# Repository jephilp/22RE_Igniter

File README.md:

# Igniter Module for Toyota VAST Engines

Hi there! This is a repository first for the 22RE igniter module, and eventually most Toyota VAST igniters. It is currently a work in progress.

# What is VAST?

VAST stands for variable advance spark timing system. It's the system Toyota uses on a ton of their older vehicles. 

## How does it work?

Here's a **very generalized** diagram to get a better idea of how the system works:

```mermaid
graph LR
A[ECU] -- IGf --> B[Igniter Module]
B -- IGt --> A
B -- NE --> A
B --> C((Ignition Coil))
C --> D{Engine}
D -- VR Signals --> B
```
## Know the flow

The way that everything ties together is fairly simple:

- At startup, the igniter assumes a locked timing. This is stated in the manual for each engine.
- The VR signal is sent to the igniter.
  - The signal is converted from a sine to a square wave by the igniter (NE).
  - NE is used to reference the spark timing for the igniter.
  - NE is also sent to the ECU for spark timing reference.
 - The ECU begins sending the IGt (Ignition Time) signal to the igniter
   - The igniter uses the **FALLING EDGE** of this signal to trigger the coil.
   - The igniter **STILL CONTROLS DWELL**. 
   - The style of signal depends on year, make and model.
 - The ECU expects to receive the IGf (Ignition Fired) signal from the igniter.
   - If the ECU does not receive this signal it will assume locked timing and issue a CEL.
   - The style of signal depends on year, make and model. 
   - This is the critical signal that blocks most ignition coil swaps.
   - The igniter can disable this signal to signify ignition issues like a bad coil. 
 - The ECU receives the signal
   - Once the signal is received within a certain time, the ECU will assume all is good.
   - The engine will run with no trouble codes as long as the timing is correct.

## Spoofing our signal

If you roam around forums long enough, you'll find that many people have figured out a way to spoof this signal. This just involves tying the IGt signal to a diode and transistor. This generates our "spoofed" IGf signal.

While this can and does work, it's not the best option. We are losing a lot of capability, and you will still need some type of module to control the coils. 

There is a better way!

## Recreating our signal

There are two main ways that our IGf signal is generated:

1. Use the overvoltage on the primary side of the coil to trigger a multivibrator that creates our signal **after** IGt.
2. Use the current through the coil to create a ramped signal **during** IGt. 

Then in the middle of all of this is our checking scheme. Failing coils won't have enough overvoltage or won't flow enough current quick enough. So ideally when our coils are failing we stop sending the IGf signal to tell the ECU to trip a CEL. 

We can create our signal using analog "dumb" logic or we can use a microcontroller for "smart" logic. Smart logic will be easier for creating a more universal module that will work with more models and allow for some tweaking.
 
## Other Options

There are some other options if your igniter fails:

- Spend $300+ on a used module from eBay or a forum member.
- Spend $500+ on an NOS module if you can find it, or import one.
- Delete the igniter system with something similar. This is only possible on some systems (22R).
- Replace the entire ECU with another that does not need IGf.
- Find an igniter delete module. This is only available for certain models and years.

# Creating our new module

Our new module will hopefully maintain original capability and add on some new capabilities as well.

The easiest way to describe creating the module is to divide up each of our signals.

## NE Signal 

Our NE signal is pretty easy to generate! For my module I am using a MAX9924 following an identical scheme to the Speeduino MAX9926 module.

You can also generate the NE signal using GM HEI modules or other off the shelf modules. There are lots of options for us here!

## IGt Signal

Our IGt signal designates when our coil will fire. From most of the information I can find, it **DOES NOT** control the dwell of the coil. So all we need to do is use the signals falling edge to control the fire point. 

I will talk about dwell control later...

## IGf Signal

The IGf signal is the critical signal here. We can:
- Use a multivibrator or microcontroller to give the ECU the duty cycle it wants when the signal **FOLLOWS  AFTER** the IGt signal.
- Use a shunt resistor to measure the current through the coil then deliver the signal to the ECU. There will be certain scaling needs to get the correct signal it wants. This is when it wants the signal **DURING** the IGt signal.

## Dwell Control

Dwell control is our final piece here. The igniter always appears to control the dwell, so unless we have an external module, we will need to control it. 

The simplest way is to depend on an IGBT controller or similar logic to begin charging and holding the current immediately after or a certain amount of time after the last spark. This is going to generate a lot of excess heat even with a current hold feature and will decrease the life on our module and coil. 

The smart way is to calculate RPM, guess when our next spark event will be, then begin charging a certain time before we expect our IGt signal. This is the best way since we will hopefully be within a few microseconds of our expected fire point and we can charge accordingly. If we use the coil current as well then we allocate extra time if our coils are taking longer than expected. There's other things we can do here too!

# Current Progress

Currently we are on the second version of the module. I will be keeping any older versions on this repo for reference, but do not encourage anyone to try building them until they are completely vetted. 

**BUILD AT YOUR OWN RISK**

## V1

V1 went about generating the IGf signal by building the circuit with only analog and passive components. It was simulated in LTSpice to verify ideal behavior before real life testing. 

While the circuit does work, it didn't yield the performance I wanted. It's also exclusive to the 53EX igniter module for the 22RTE, so it's not the best to be developing as a universal module.

## V2

V2 is instead intended to be changed and modified for as many igniter modules as possible: 
- It uses an ATTINY841 chip to do all of our calculations and logic. 
- It is mostly chosen for ease of use and 5V logic, there are buffers as well for output protection.
- The IGBT is controlled through a FAN1100 Ignition IGBT controller. This is much easier than a custom control scheme and relieves processing from our MCU.
- Currently has an analog switch to swap between using NE and the MCU for IGBT control. This is a failsafe but there may be a better way to go about it.
- Each chunk is made to be modular. If someone needs 3 more outputs then they can multiple the output circuit 3 more times and use a similar MCU. 

Overall this is still a work in progress. My ECU and original Igniter are out for repair and testing, so I am unable to verify the new design until I get them back.

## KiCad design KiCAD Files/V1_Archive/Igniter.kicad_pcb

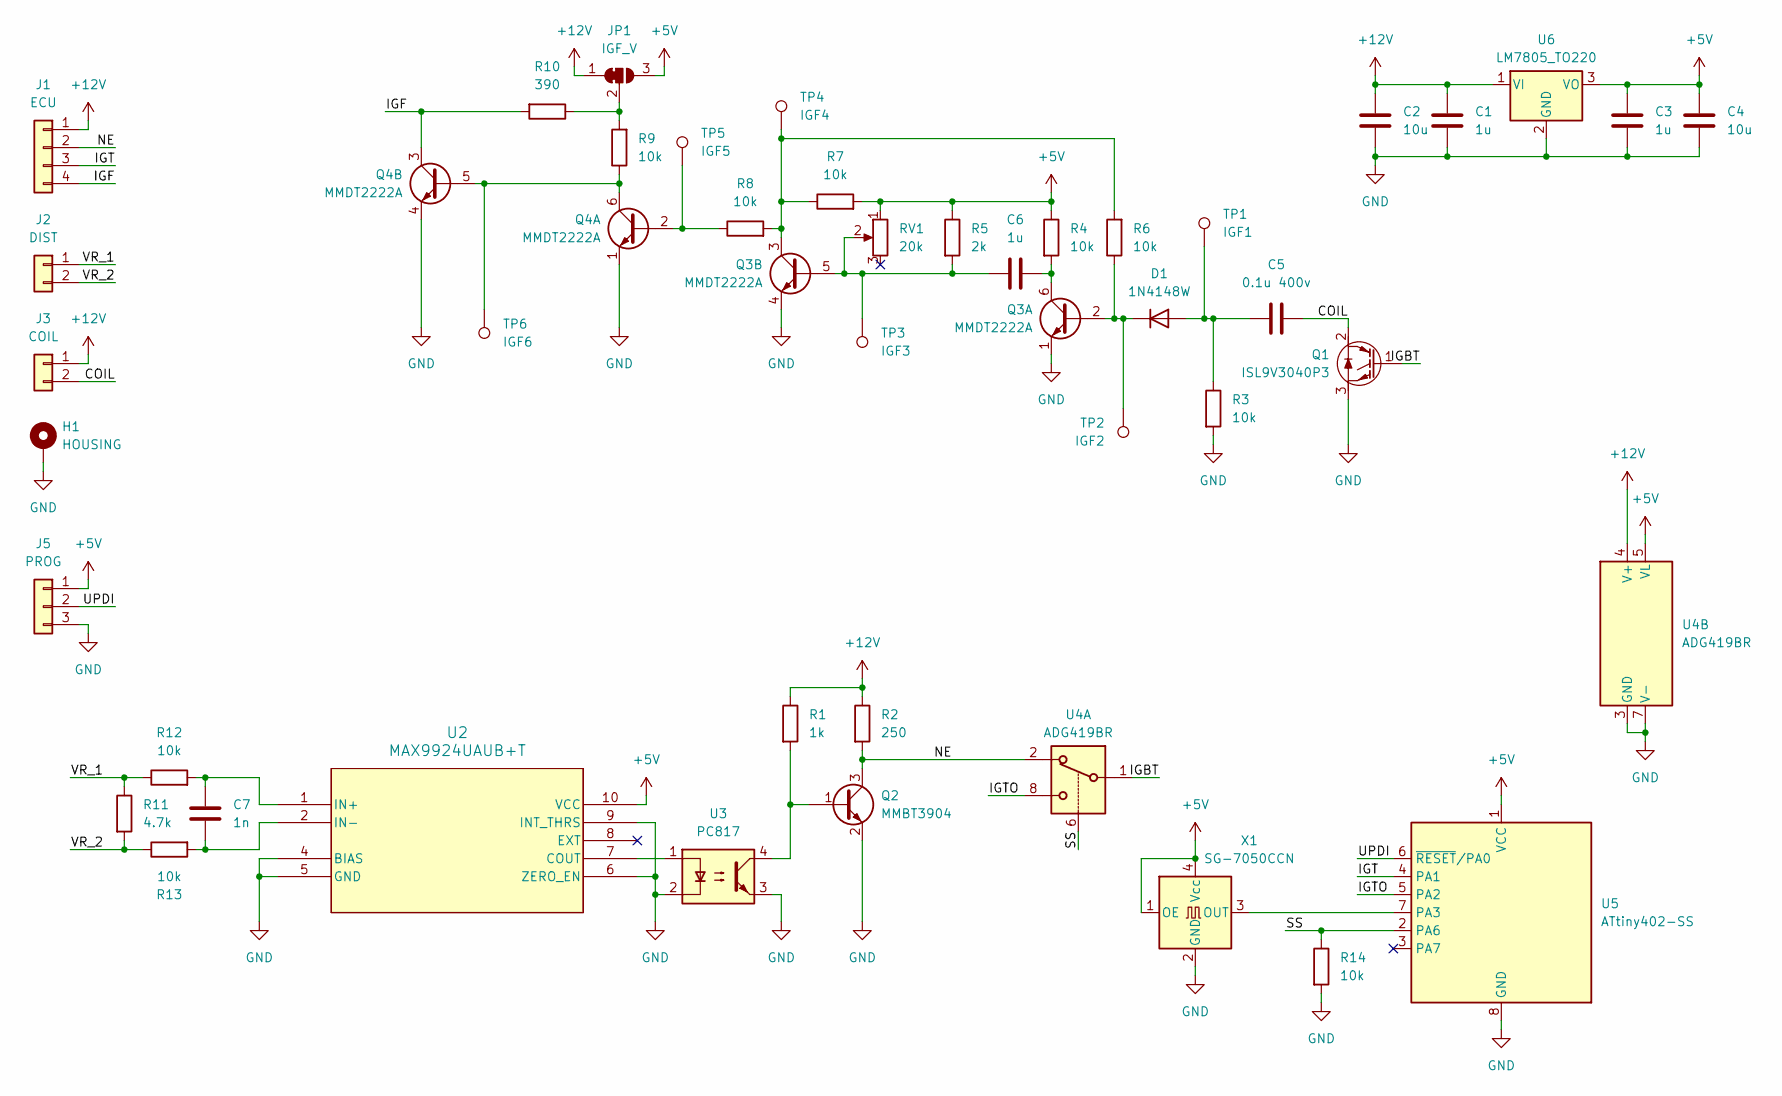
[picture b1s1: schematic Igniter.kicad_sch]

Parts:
C1, C3, C6: 1u; C_0805_2012Metric
C2, C4: 10u; C_0805_2012Metric
C5: 0.1u 400v; C_0805_2012Metric
C7: 1n; C_0805_2012Metric
D1: 1N4148W; D_SOD-123
H1: HOUSING; MountingHole_3.2mm_M3_Pad
J1: ECU; PinHeader_1x04_P2.54mm_Vertical
J2: DIST; PinHeader_1x02_P2.54mm_Vertical
J3: COIL; SolderWire-1sqmm_1x02_P5.4mm_D1.4mm_OD2.7mm
J5: PROG; PinHeader_1x03_P2.54mm_Vertical
JP1: IGF_V; SolderJumper-3_P1.3mm_Bridged12_Pad1.0x1.5mm_NumberLabels
Q1: ISL9V3040P3; TO-220-3_Vertical
Q2: MMBT3904; SOT-23
Q3, Q4: MMDT2222A; SOT-363_SC-70-6
R1: 1k; R_0805_2012Metric
R2: 250; R_0805_2012Metric
R3, R4, R6, R7, R8, R9, R12, R13, R14: 10k; R_0805_2012Metric
R5: 2k; R_0805_2012Metric
R10: 390; R_0805_2012Metric
R11: 4.7k; R_0805_2012Metric
RV1: 20k; Potentiometer_Bourns_3296W_Vertical
TP1: IGF1; TestPoint_THTPad_D1.0mm_Drill0.5mm
TP2: IGF2; TestPoint_THTPad_D1.0mm_Drill0.5mm
TP3: IGF3; TestPoint_THTPad_D1.0mm_Drill0.5mm
TP4: IGF4; TestPoint_THTPad_D1.0mm_Drill0.5mm
TP5: IGF5; TestPoint_THTPad_D1.0mm_Drill0.5mm
TP6: IGF6; TestPoint_THTPad_D1.0mm_Drill0.5mm
U2: MAX9924UAUB+T; MSOP-10_3x3mm_P0.5mm
U3: PC817; DIP-4_W7.62mm
U4: ADG419BR; SOIC-8_3.9x4.9mm_P1.27mm
U5: ATtiny402-SS; SOIC-8_3.9x4.9mm_P1.27mm
U6: LM7805_TO220; TO-220-3_Vertical
X1: SG-7050CCN; Oscillator_SMD_SeikoEpson_SG8002CA-4Pin_7.0x5.0mm

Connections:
+5V: C3.1, C4.1, J5.1, JP1.3 (B), R4.1, R5.1, R7.2, RV1.1, U2.10 (VCC), U4.5 (VL), U5.1 (VCC), U6.3 (VO), X1.1 (OE), X1.4 (Vcc)
+12V: C1.1, C2.1, J1.1, J3.1, JP1.1 (A), R1.1, R2.1, U4.4 (V+), U6.1 (VI)
/COIL: C5.2, J3.2, Q1.2 (C)
/IGBT: Q1.1 (G), U4.1
/IGF: J1.4, Q4.3 (C2), R10.2
/IGT: J1.3, U5.4 (PA1)
/IGTO: U4.8, U5.5 (PA2)
/NE: J1.2, Q2.3 (C), R2.2, U4.2
/SS: R14.1, U4.6, U5.2 (PA6)
/UPDI: J5.2, U5.6 (~RESET/PA0)
/VR_1: J2.1, R11.1, R12.1
/VR_2: J2.2, R11.2, R13.1
GND: C1.2, C2.2, C3.2, C4.2, H1.1, J5.3, Q1.3 (E), Q2.2 (E), Q3.1 (E1), Q3.4 (E2), Q4.1 (E1), Q4.4 (E2), R3.2, R14.2, U2.4 (BIAS), U2.5 (GND), U2.6 (ZERO_EN), U2.9 (INT_THRS), U3.2, U3.3, U4.3 (GND), U4.7 (V-), U5.8 (GND), U6.2 (GND), X1.2 (GND)
unnamed: C5.1, D1.2 (A), R3.1, TP1.1
unnamed: D1.1 (K), Q3.2 (B1), R6.1, TP2.1
unnamed: JP1.2 (C), R9.2, R10.1
unnamed: Q2.1 (B), R1.2, U3.4
unnamed: C6.2, Q3.6 (C1), R4.2
unnamed: C6.1, Q3.5 (B2), R5.2, RV1.2, TP3.1
unnamed: Q3.3 (C2), R6.2, R7.1, R8.2, TP4.1
unnamed: Q4.2 (B1), R8.1, TP5.1
unnamed: Q4.5 (B2), Q4.6 (C1), R9.1, TP6.1
unnamed: U2.7 (COUT), U3.1
unnamed: C7.1, R12.2, U2.1 (IN+)
unnamed: C7.2, R13.2, U2.2 (IN-)
unnamed: U5.7 (PA3), X1.3 (OUT)

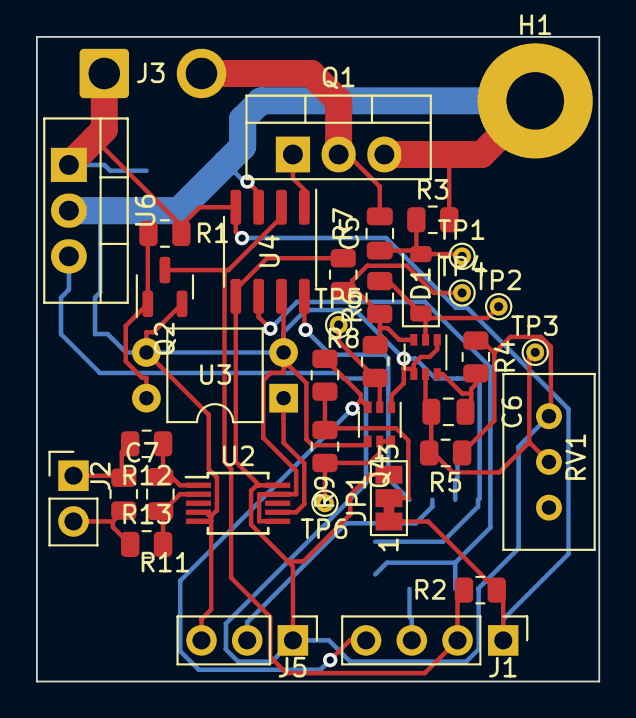
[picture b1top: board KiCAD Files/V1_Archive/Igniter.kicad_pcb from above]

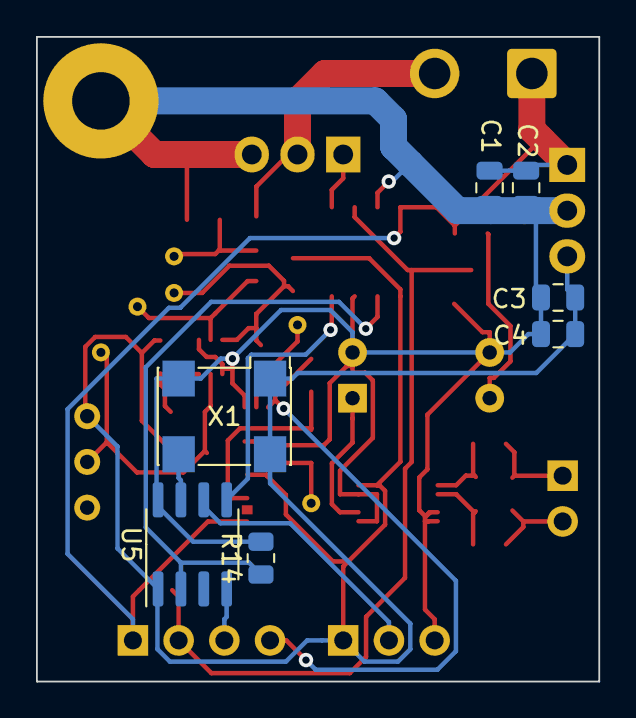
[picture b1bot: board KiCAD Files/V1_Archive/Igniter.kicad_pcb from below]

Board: 2 copper layers, 31.2 x 35.8 mm, 45 parts (7 on the bottom side), 26 nets.

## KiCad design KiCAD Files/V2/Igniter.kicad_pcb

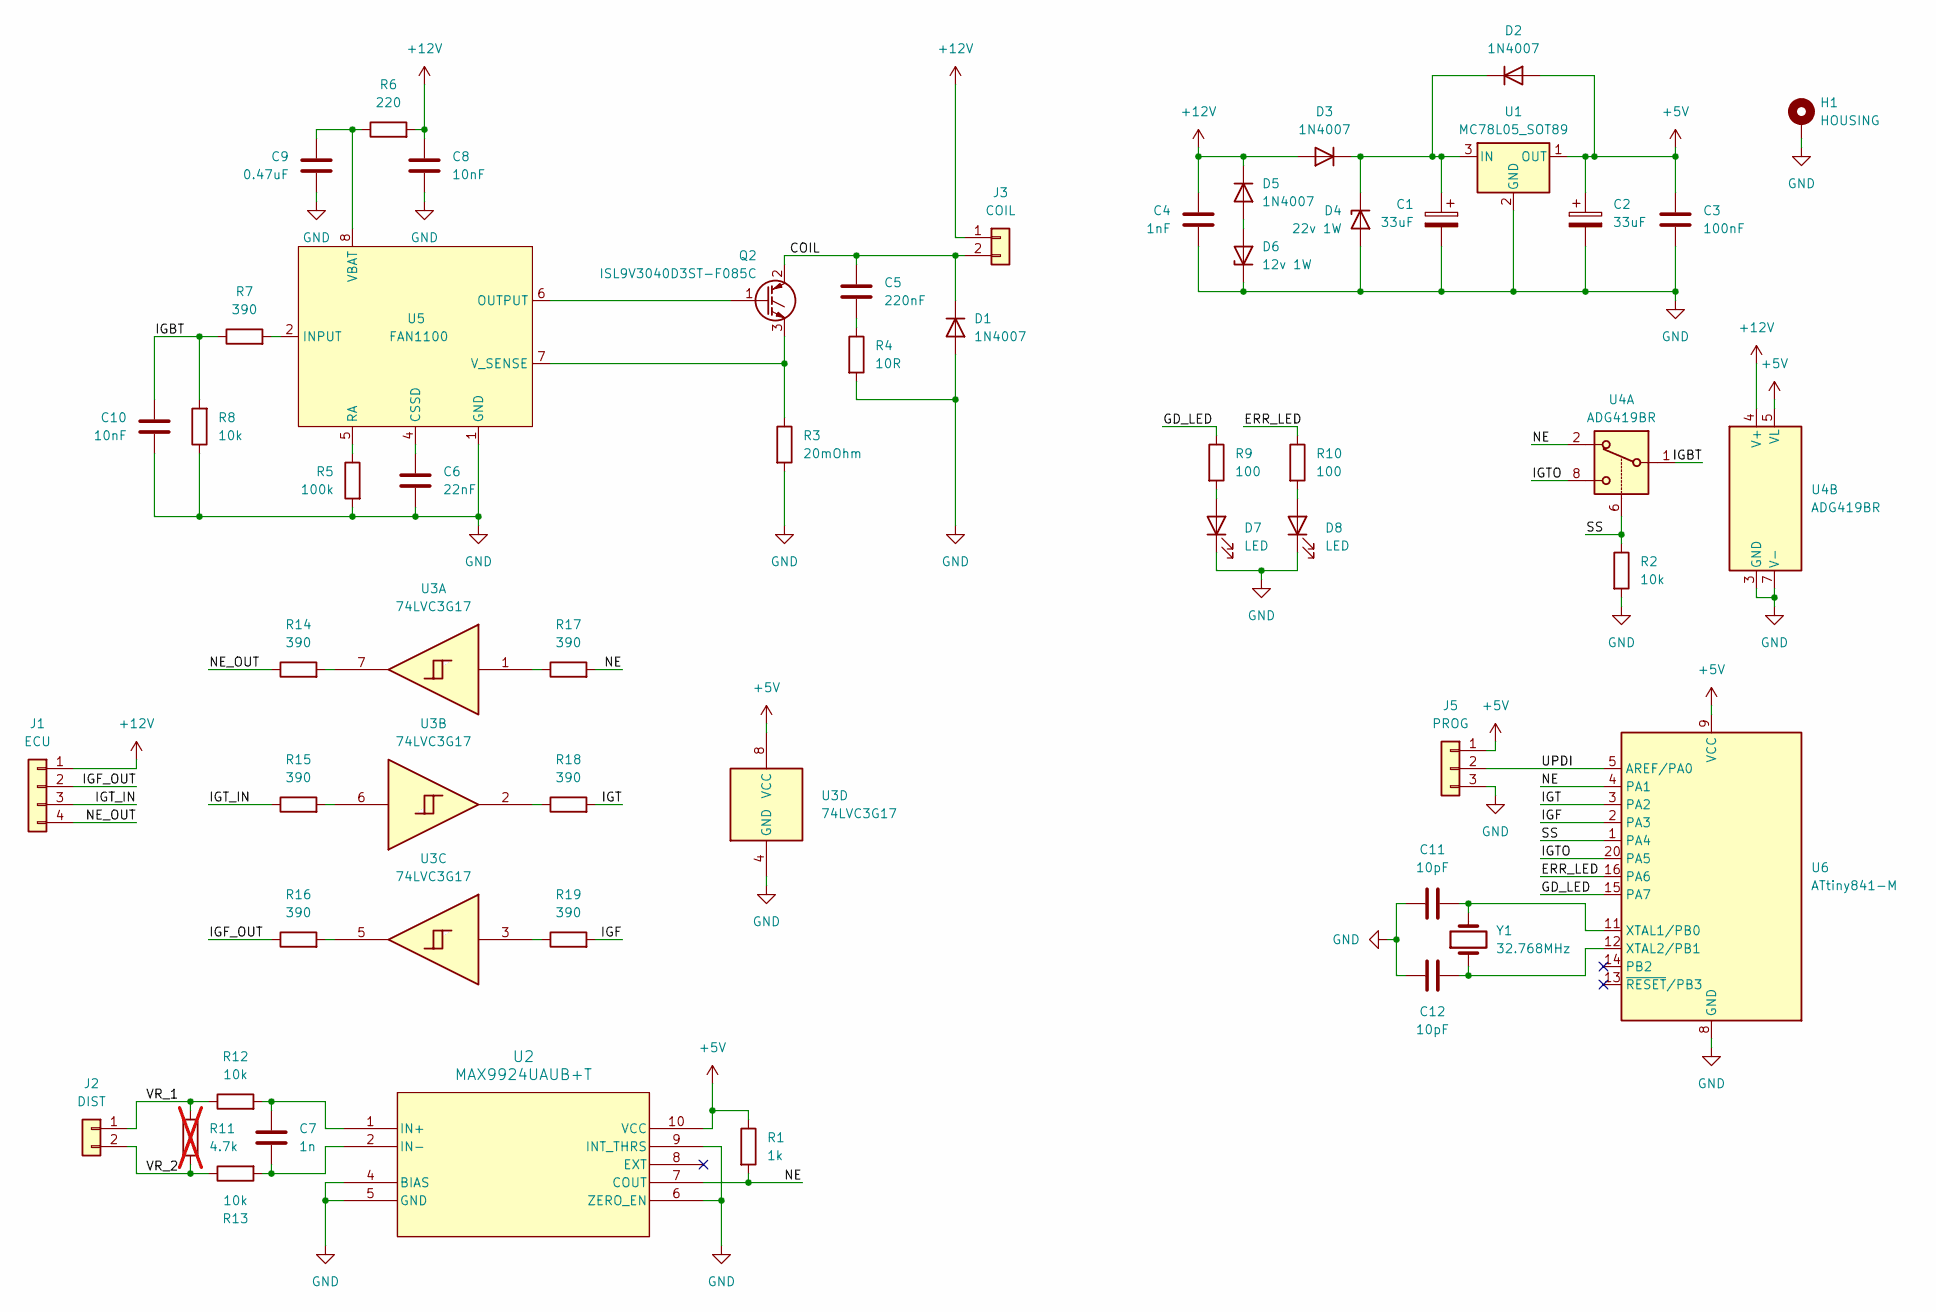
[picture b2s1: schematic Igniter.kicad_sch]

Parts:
C1, C2: 33uF; CP_EIA-7343-30_AVX-N
C3: 100nF; C_0805_2012Metric
C4: 1nF; C_0805_2012Metric
C5: 220nF; C_0805_2012Metric
C6: 22nF; C_0805_2012Metric
C7: 1n; C_0805_2012Metric
C8, C10: 10nF; C_0805_2012Metric
C9: 0.47uF; C_0805_2012Metric
C11, C12: 10pF; C_0805_2012Metric
D1, D2, D3, D5: 1N4007; D_SMF
D4: 22v 1W; D_SMF
D6: 12v 1W; D_SMF
D7, D8: LED; LED_0805_2012Metric
H1: HOUSING; MountingHole_3.2mm_M3_Pad
J1: ECU; PinHeader_1x04_P2.54mm_Vertical
J2: DIST; PinHeader_1x02_P2.54mm_Vertical
J3: COIL; SolderWire-1sqmm_1x02_P5.4mm_D1.4mm_OD2.7mm
J5: PROG; PinHeader_1x03_P2.54mm_Vertical
Q2: ISL9V3040D3ST-F085C; TO-252-2
R1: 1k; R_0603_1608Metric
R2, R8: 10k; R_0603_1608Metric
R3: 20mOhm; R_1206_3216Metric
R4: 10R; R_0805_2012Metric
R5: 100k; R_0603_1608Metric
R6: 220; R_0603_1608Metric
R7, R14, R15, R16, R17, R18, R19: 390; R_0603_1608Metric
R9, R10: 100; R_0603_1608Metric
R11: 4.7k; R_0805_2012Metric; not fitted
R12, R13: 10k; R_0805_2012Metric
U1: MC78L05_SOT89; SOT-89-3
U2: MAX9924UAUB+T; MSOP-10_3x3mm_P0.5mm
U3: 74LVC3G17; VSSOP-8_2.4x2.1mm_P0.5mm
U4: ADG419BR; SOIC-8_3.9x4.9mm_P1.27mm
U5: FAN1100; SOIC-8_3.9x4.9mm_P1.27mm
U6: ATtiny841-M; QFN-20-1EP_4x4mm_P0.5mm_EP2.6x2.6mm
Y1: 32.768MHz; Crystal_SMD_3215-2Pin_3.2x1.5mm

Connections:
+5V: C2.1, C3.1, D2.2 (A), J5.1, R1.1, U1.1 (OUT), U2.10 (VCC), U3.8 (VCC), U4.5 (VL), U6.9 (VCC)
+12V: C4.1, C8.1, D3.2 (A), D5.1 (K), J1.1, J3.1, R6.2, U4.4 (V+)
/COIL: C5.1, D1.1 (K), J3.2, Q2.2 (C)
/ERR_LED: R10.1, U6.16 (PA6)
/GD_LED: R9.1, U6.15 (PA7)
/IGBT: C10.1, R7.1, R8.2, U4.1
/IGF: R19.2, U6.2 (PA3)
/IGF_OUT: J1.2, R16.1
/IGT: R18.2, U6.3 (PA2)
/IGTO: U4.8, U6.20 (PA5)
/IGT_IN: J1.3, R15.1
/NE: R1.2, R17.2, U2.7 (COUT), U4.2, U6.4 (PA1)
/NE_OUT: J1.4, R14.1
/SS: R2.1, U4.6, U6.1 (PA4)
/UPDI: J5.2, U6.5 (AREF/PA0)
/VR_1: J2.1, R11.1, R12.1
/VR_2: J2.2, R11.2, R13.1
GND: C1.2, C2.2, C3.2, C4.2, C6.2, C8.2, C9.2, C10.2, C11.1, C12.1, D1.2 (A), D4.2 (A), D6.1 (K), D7.1 (K), D8.1 (K), H1.1, J5.3, R2.2, R3.2, R4.2, R5.2, R8.1, U1.2 (GND), U2.4 (BIAS), U2.5 (GND), U2.6 (ZERO_EN), U2.9 (INT_THRS), U3.4 (GND), U4.3 (GND), U4.7 (V-), U5.1 (GND), U6.8 (GND), U6.21 (GND)
unnamed: C5.2, R4.1
unnamed: C1.1, D2.1 (K), D3.1 (K), D4.1 (K), U1.3 (IN)
unnamed: D5.2 (A), D6.2 (A)
unnamed: D7.2 (A), R9.2
unnamed: D8.2 (A), R10.2
unnamed: Q2.3 (E), R3.1, U5.7 (V_SENSE)
unnamed: Q2.1 (G), U5.6 (OUTPUT)
unnamed: R14.2, U3.7
unnamed: R15.2, U3.6
unnamed: R16.2, U3.5
unnamed: R17.1, U3.1
unnamed: R18.1, U3.2
unnamed: R19.1, U3.3
unnamed: C7.1, R12.2, U2.1 (IN+)
unnamed: C7.2, R13.2, U2.2 (IN-)
unnamed: C6.1, U5.4 (CSSD)
unnamed: R7.2, U5.2 (INPUT)
unnamed: R5.1, U5.5 (RA)
unnamed: C9.1, R6.1, U5.8 (VBAT)
unnamed: C11.2, U6.11 (XTAL1/PB0), Y1.2
unnamed: C12.2, U6.12 (XTAL2/PB1), Y1.1

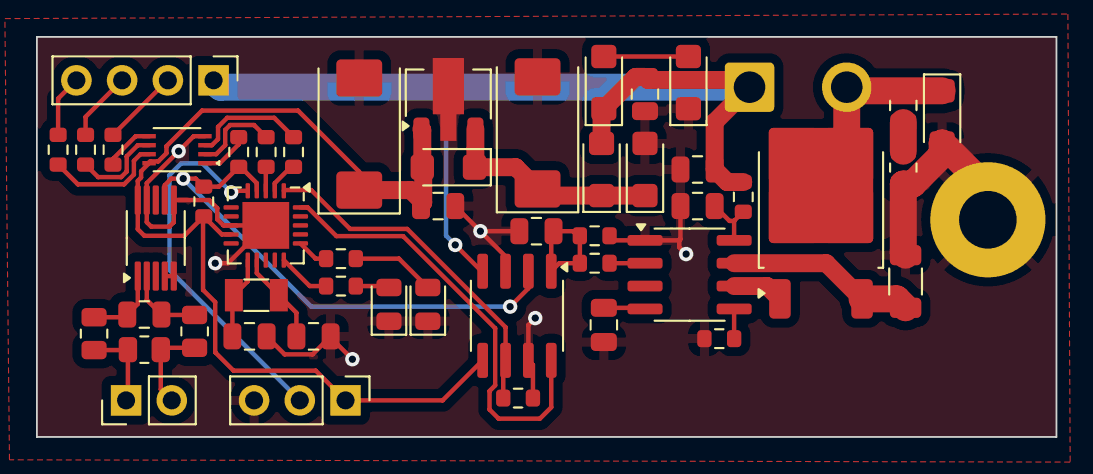
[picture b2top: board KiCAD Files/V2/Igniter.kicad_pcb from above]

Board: 2 copper layers, 56.6 x 22.2 mm, 52 parts (0 on the bottom side), 39 nets.

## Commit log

2024-01-08 Added KiCAD and Spice
    Added board files and spice model for the IGF circuit.
2024-07-24 Added V2 version of PCB
    Changed gears to make the whole module more modular for different engines.
